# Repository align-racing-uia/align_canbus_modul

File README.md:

<h1 align="center"> Align CANBus Module [REQUIRE CLEANUP]</h1> <br>
<p align="center">
    
</p>

<!-- START doctoc generate TOC please keep comment here to allow auto update -->
<!-- DON'T EDIT THIS SECTION, INSTEAD RE-RUN doctoc TO UPDATE -->
## Table of contents

- [Introduction](#introduction)
- [Align Racing UiA](#alignracinguia)
- [Rules for file structure](#rulesforfilestructure)
- [License](#license)

<!-- END doctoc generated TOC please keep comment here to allow auto update -->

## Introduction

This is the repository for Align Racing's formula student race car's different systems.

## Align Racing UiA

<a href="http://www.alignracing.no/">Align Racing UiA (AR)</a> is a multidisciplinary student organisation at <a href="https://www.uia.no/">The University of Agder (UiA)</a>, that take part in the world’s largest yearly engineering competition; <a href="https://www.imeche.org/events/formula-student">Formula Student (FS)</a>. The organisation continuously consists of around 60 students, from a wide variety of disciplines. The competition includes developing, building, budgeting and marketing a small scale formula type racing car. AR takes this a bit further by having more focus on developing a strong organisation, open for all disciplines, that gives the members a taste of future work-life.

## ACM 2020

### Changelog:

**27.07.2019:**
- Added: Protection circuit
- Added: Atmega Clock pass-through
- Moved: External oscillator from MCP to Atmega.

**28.07.2019:**
- Changed:	Orientation of tag connector in schematics
- Added:	Connector with I/O
- Added:	Overcurrent protection with polyfuse
- Added:	Overvoltage protection with zener diode
- Added:	Reverse polarity protection with diode
- Generated:Bill of Materials
- Added:	JAE IL-WX Series 0.8mm Pitch 30 Way connector
- Added:	RGB LED
- Added: P-mosfet for reverse polarity-protection
- Positioned power management (OC, OV, RP) in a 12x4mm space.
- Started tracing

**29.07.2019:**
- Moved: Protection circuit
- Changed board layout
- Changed viasize from 0.2 to 0.3
- Routing of tracks

**30.07.2019:**
- Added 3D components
- Removed all Tracks
- Added DC/DC converter
- Changed footprint of connector
- Added LP-filter to Atmega Avcc (Datasheet page 348)

**03.08.2019:**
- Changed folder structure
- Added mounting hole in schematics
- Removed LDO
- Added 5V switching regulator
- Changed Connector footprint
- Added track and via info from JLCPCB (2-Layers)

**04.08.2019:**
- Completed BOM on Google Drive
- Added 2x 10uF input Capacitor for regulator
- Moved documentation to main

**06.10.2019:**
- Moved resistors and capacitors away from microcontrollers
- Changed from Atmega328PB to Atmega328P (NB! Need to check circuit PWM and such)
- Disconnected all output pins on the Atmega328P
- Created a ACM simulation folder
- Connected pins that are equal to Atmega328PB

### ACM 2019 - Documentation

List of possible imporvements for ACM 2019
  + Remove the Fuse as it is 20\% of the total cost. Change it to a soldered SMD fuse or a diode.
   % Soruce https://docs.google.com/spreadsheets/d/1aR7CLCnCkN-1Qp3qICuXivDnihjTyPiA6Gjus2cEa0c/edit#gid=311613741&range=R12:R13
  
  + More I/O (Especially 2 interrupt) or change board dimension ratio. (1:1) like a flight controller
  
  + Remove castellated holes, since it makes the boards less reliable, and are also harder to manufacture.  
  
  + Change the led to a larger led for easy board manufacturing.
  
  + Change I/O to only one side of the board for hot swap.
  
  + ICSP take a large amout of space, change it to pads or small programming connector.
  
  + Change the width of the PCB to X*2,54mm so that it fits standard pin layout
  
  + Remove clock capacitors as "CSTNE16M0V530000R0" got 15uF embedded. Doesn't not require external load capacitors
  
  + Add a diode with a capacitor after. ACM reset due to low voltage when high current draw.
  
  + Possibility for UART out
  
  + Add low pass filter for the A/D converter (AVcc input) (See page 14 in 328p datasheet)
  
## License
All content included in this Git repository is under the license:

Creative Commons Attribution-NonCommercial-ShareAlike 4.0 International

You are free to:
* <b> Share </b> — copy and redistribute the material in any medium or format
* <b> Adapt </b> — remix, transform, and build upon the material

Under the following terms:
* <b> Attribution </b> — You must give appropriate credit, provide a link to the license, and indicate if changes were made. You may do so in any reasonable manner, but not in any way that suggests the licensor endorses you or your use.
* <b> NonCommercial </b> — You may not use the material for commercial purposes.
* <b> ShareAlike </b> — If you remix, transform, or build upon the material, you must distribute your contributions under the same license as the original.
* <b> No additional restrictions </b> — You may not apply legal terms or technological measures that legally restrict others from doing anything the license permits.

>>>>>>> master

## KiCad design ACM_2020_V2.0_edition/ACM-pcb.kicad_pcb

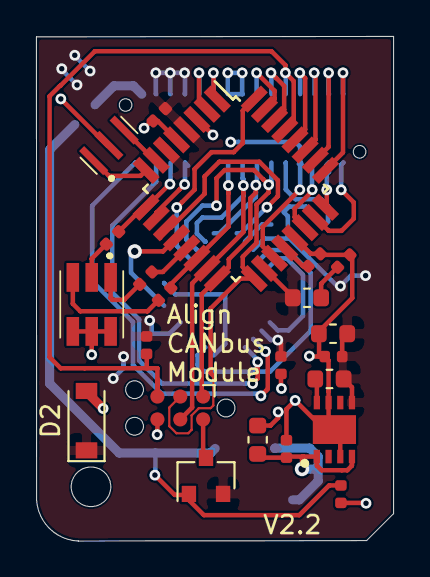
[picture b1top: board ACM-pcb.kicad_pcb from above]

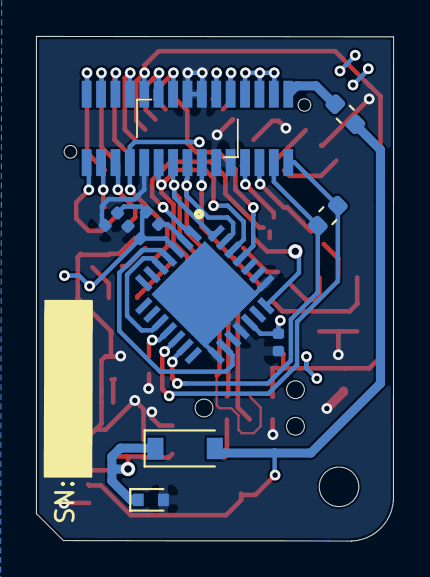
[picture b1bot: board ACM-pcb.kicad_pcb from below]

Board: 2 copper layers, 19.8 x 28.0 mm, 33 parts (11 on the bottom side), 42 nets.

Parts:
C1, C2, C3, C4, C5, C6, C7, C8, C9: 0.1uF; C_0402_1005Metric
C10, C11: 10uF; C_0603_1608Metric
D1: 15V; D_SOD-523
D2: D_Zener_KDZVTR5.6B; D_Zener_KDZV5.6B_SOD-123
D4: D_Schottky_MBR0520LT1G; D_schotky_MBR0520LT1G
F1: 250mA; Fuse_0603_1608Metric
H1: M2 Mouting hole; MountingHole_2.2mm_M2
IC1: MCP25625T-E_ML; QFN65P600X600X100-29N-D
J1: TC2030-MCP-NL; Tag-Connect_TC2030-IDC-NL_2x03_P1.27mm_Vertical
L1: 10uH; L_0603_1608Metric
L2: 2.2 µH; L_0603_1608Metric
LED1: ASMB-TTF0-0A20B; ASMBTTF00A20B
P1: Conn_02x15_Odd_Even; ILWX10SBVFBE
Q1: Q_PMOS_DMP3099L-13; Pmos_DMP3099L-13
R1, R2, R6: 10K Ohm; R_0402_1005Metric
R3: 290 ohm; R_0402_1005Metric
R4: 200ohm; R_0402_1005Metric
R5: 190 Ohm; R_0402_1005Metric
R7: 120 Ohm; R_0603_1608Metric
U1: ATmega328P-AU; TQFP-32_7x7mm_P0.8mm
U3: NCV890430MW50TXG; SON65P300X300X100-9N
Y1: 16.0Mhz; CSTNE16M0V530000R0

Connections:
12V_fused: D4.2, F1.1, Q1.1, R2.2
+5V: C1.1, C5.1, C6.1, C7.1, C8.1, C9.2, C11.1, D2.1, IC1.3, IC1.11, IC1.19, L1.1, L2.2, P1.24, P1.26, P1.28, Q1.2, R1.1, R6.2, U1.4, U1.6, U1.18, U3.5
+12V: F1.2, P1.30
+12V_Safe: C4.1, C10.1, D1.1, D4.1, U3.1, U3.4
/BLUE_LED: P1.17, R5.2, U1.14
/CAN_CS: IC1.1, U1.11
/CAN_INT: IC1.25, U1.32
/CLK_MCP: IC1.21, U1.12
/GREEN_LED: P1.25, R4.2, U1.9
/MISO: IC1.28, J1.1, P1.13, U1.16
/MOSI: IC1.27, J1.4, P1.15, U1.15
/RED_LED: R3.2, U1.13
/Reset: J1.5, P1.10, R1.2, U1.29
/SCK: IC1.26, J1.3, P1.11, U1.17
/U-Pin1: P1.1, U1.23
/U-Pin2: P1.2, U1.25
/U-Pin3: P1.3, U1.24
/U-Pin4: P1.4, U1.26
/U-Pin5: P1.5, U1.22
/U-Pin6: P1.6, U1.27
/U-Pin7: P1.7, U1.19
/U-Pin8: P1.8, U1.28
/U-Pin12: P1.12, U1.30
/U-Pin14: P1.14, U1.31
/U-Pin20: P1.20, U1.1
/U-Pin22: P1.22, U1.2
/U-Pin23: P1.23, U1.10
/U-Pin27: IC1.13, P1.27, R7.1
/U-Pin29: IC1.12, P1.29, R7.2
GND: C1.2, C2.2, C3.1, C4.2, C5.2, C6.2, C7.2, C8.2, C9.1, C10.2, C11.2, D1.2, D2.2, IC1.15, IC1.18, IC1.22, IC1.29, J1.6, LED1.2, LED1.4, LED1.6, P1.9, P1.16, P1.18, P1.19, P1.21, R2.1, U1.3, U1.5, U1.21, U3.3, U3.7, U3.9, Y1.2
unnamed: C2.1, U1.20
unnamed: C3.2, L1.2
unnamed: IC1.2, R6.1
unnamed: IC1.5, IC1.10
unnamed: IC1.4, IC1.16
unnamed: J1.2, Q1.3
unnamed: L2.1, U3.8
unnamed: LED1.1, R3.1
unnamed: LED1.3, R4.1
unnamed: LED1.5, R5.1
unnamed: U1.7, Y1.3
unnamed: U1.8, Y1.1

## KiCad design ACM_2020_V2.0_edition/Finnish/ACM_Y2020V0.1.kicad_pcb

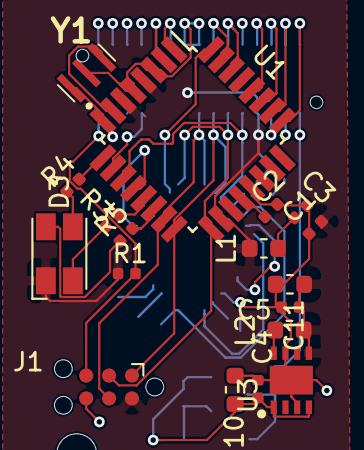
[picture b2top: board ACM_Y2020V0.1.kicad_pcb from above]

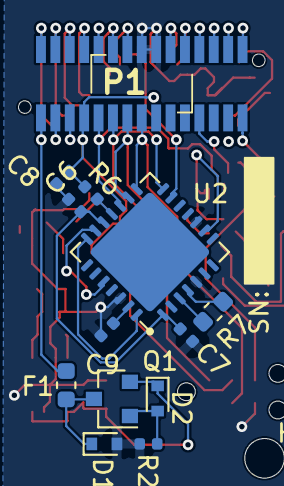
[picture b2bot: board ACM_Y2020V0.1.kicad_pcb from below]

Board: 2 copper layers, 32 parts (14 on the bottom side), 40 nets.

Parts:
C1, C2, C3, C4, C5, C6, C7, C8, C9: 0.1uF; C_0402_1005Metric
C10, C11: 10uF; C_0603_1608Metric
D1: 15V; D_SOD-523
D2: 2.4V; D_SOD-523
D3: ASMB-MTB0-0A3A2; LED_Avago_PLCC4_3.2x2.8mm_CW
F1: 250mA; Fuse_0603_1608Metric
H1: M2 Mouting hole; MountingHole_2.2mm_M2
J1: TC2030-MCP-NL; Tag-Connect_TC2030-IDC-NL_2x03_P1.27mm_Vertical
L1: 10uH; L_0603_1608Metric
L2: 2.2 µH; L_0603_1608Metric
P1: Conn_02x15_Odd_Even; ILWX10SBVFBE
Q1: Q_PMOS_DGS; SOT-23
R1, R6: 10K Ohm; R_0402_1005Metric
R2: 100K Ohm; R_0402_1005Metric
R3: 290 ohm; R_0402_1005Metric
R4: 200ohm; R_0402_1005Metric
R5: 190 Ohm; R_0402_1005Metric
R7: 120 Ohm; R_0603_1608Metric
U1: ATmega328P-AU; TQFP-32_7x7mm_P0.8mm
U2: MCP25625-x-SS; QFN-28-1EP_6x6mm_P0.65mm_EP4.8x4.8mm
U3: NCV890430MW50TXG; SON65P300X300X100-9N
Y1: 16.0Mhz; CSTNE16M0V530000R0

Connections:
+5V: C1.1, C5.1, C6.1, C11.1, D3.1, J1.2, L1.1, L2.2, P1.7, R1.1, R6.2, U1.4, U1.6, U1.18, U3.5
+12V: F1.2, P1.1
+12V_Safe: C4.1, C10.1, D2.1, Q1.2, U3.1, U3.4
/BLUE_LED: R5.2, U1.14
/CAN_CS: P1.9, U1.11, U2.17
/CAN_INT: U1.32, U2.13
/CLK_MCP: U1.12, U2.9
/GREEN_LED: R4.2, U1.9
/MISO: J1.1, P1.13, U1.16, U2.16
/MOSI: J1.4, P1.15, U1.15, U2.15
/RED_LED: R3.2, U1.13
/Reset: J1.5, P1.29, R1.2
/SCK: J1.3, P1.11, U1.17, U2.14
/U-Pin1: R7.2, U2.3
/U-Pin2: P1.2, U1.25
/U-Pin3: R7.1, U2.4
/U-Pin4: P1.4, U1.26
/U-Pin6: P1.6, U1.27
/U-Pin8: P1.8, U1.28
/U-Pin12: P1.12, U1.30
/U-Pin14: P1.14, U1.31
/U-Pin20: P1.20, U1.1
/U-Pin22: P1.22, U1.2
/U-Pin23: P1.23, U1.10
GND: C1.2, C2.2, C3.1, C4.2, C5.2, C6.2, C7.2, C8.2, C9.1, C10.2, C11.2, D1.2, J1.6, P1.16, P1.18, R2.2, U1.3, U1.5, U1.21, U2.5, U2.10, U2.26, U3.3, U3.7, U3.9, Y1.2
unnamed: C2.1, U1.20
unnamed: C3.2, L1.2
unnamed: C7.1, C8.1, U2.1, U2.19
unnamed: C9.2, U2.27
unnamed: D1.1, F1.1, Q1.3
unnamed: D2.2, Q1.1, R2.1
unnamed: D3.2, R5.1
unnamed: D3.3, R4.1
unnamed: D3.4, R3.1
unnamed: L2.1, U3.8
unnamed: R6.1, U2.18
unnamed: U1.7, Y1.3
unnamed: U1.8, Y1.1
unnamed: U2.20, U2.24
unnamed: U2.21, U2.28

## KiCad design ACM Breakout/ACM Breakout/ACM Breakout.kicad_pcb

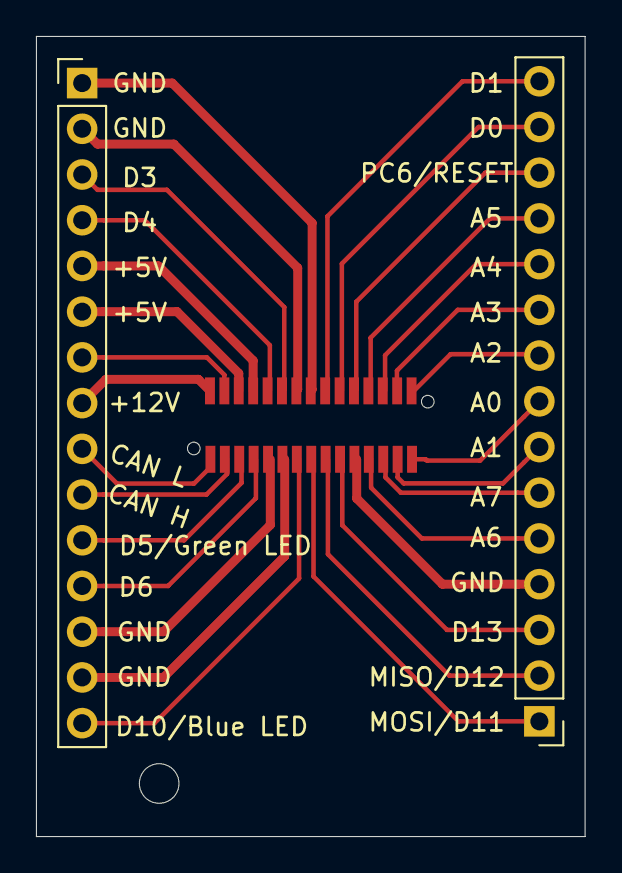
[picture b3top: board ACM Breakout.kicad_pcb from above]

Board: 2 copper layers, 30.5 x 44.5 mm, 3 parts (0 on the bottom side), 30 nets.

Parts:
J1, J2: Conn_01x15_Male; PinHeader_1x15_P2.54mm_Vertical
U1: ACM_2020; ACM_2020_Footprint_wo_silk

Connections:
/Pin1: J2.8, U1.1
/Pin2: J2.9, U1.2
/Pin3: J2.7, U1.3
/Pin4: J2.10, U1.4
/Pin5: J2.6, U1.5
/Pin6: J2.11, U1.6
/Pin7: J2.5, U1.7
/Pin8: J2.12, U1.8
/Pin9: J2.4, U1.9
/Pin10: J2.13, U1.10
/Pin11: J2.3, U1.11
/Pin12: J2.14, U1.12
/Pin13: J2.2, U1.13
/Pin14: J2.15, U1.14
/Pin15: J2.1, U1.15
/Pin16: J1.1, U1.16
/Pin17: J1.15, U1.17
/Pin18: J1.2, U1.18
/Pin19: J1.14, U1.19
/Pin20: J1.3, U1.20
/Pin21: J1.13, U1.21
/Pin22: J1.4, U1.22
/Pin23: J1.12, U1.23
/Pin24: J1.5, U1.24
/Pin25: J1.11, U1.25
/Pin26: J1.6, U1.26
/Pin27: J1.10, U1.27
/Pin28: J1.7, U1.28
/Pin29: J1.9, U1.29
/Pin30: J1.8, U1.30

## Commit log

2021-07-15 Adjuster folder structure and README.md
2021-07-15 Adjusted folder structure.
2021-08-01 Move everything in main.
2021-08-01 Move everything in main. And delete directories.
2021-08-01 .idea generated and added.
2021-08-01 This repo require cleanup.
